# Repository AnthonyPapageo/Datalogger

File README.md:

# Datalogger
Datalogger with LCD interface

TFE Bachelier, c'était cool Thales !

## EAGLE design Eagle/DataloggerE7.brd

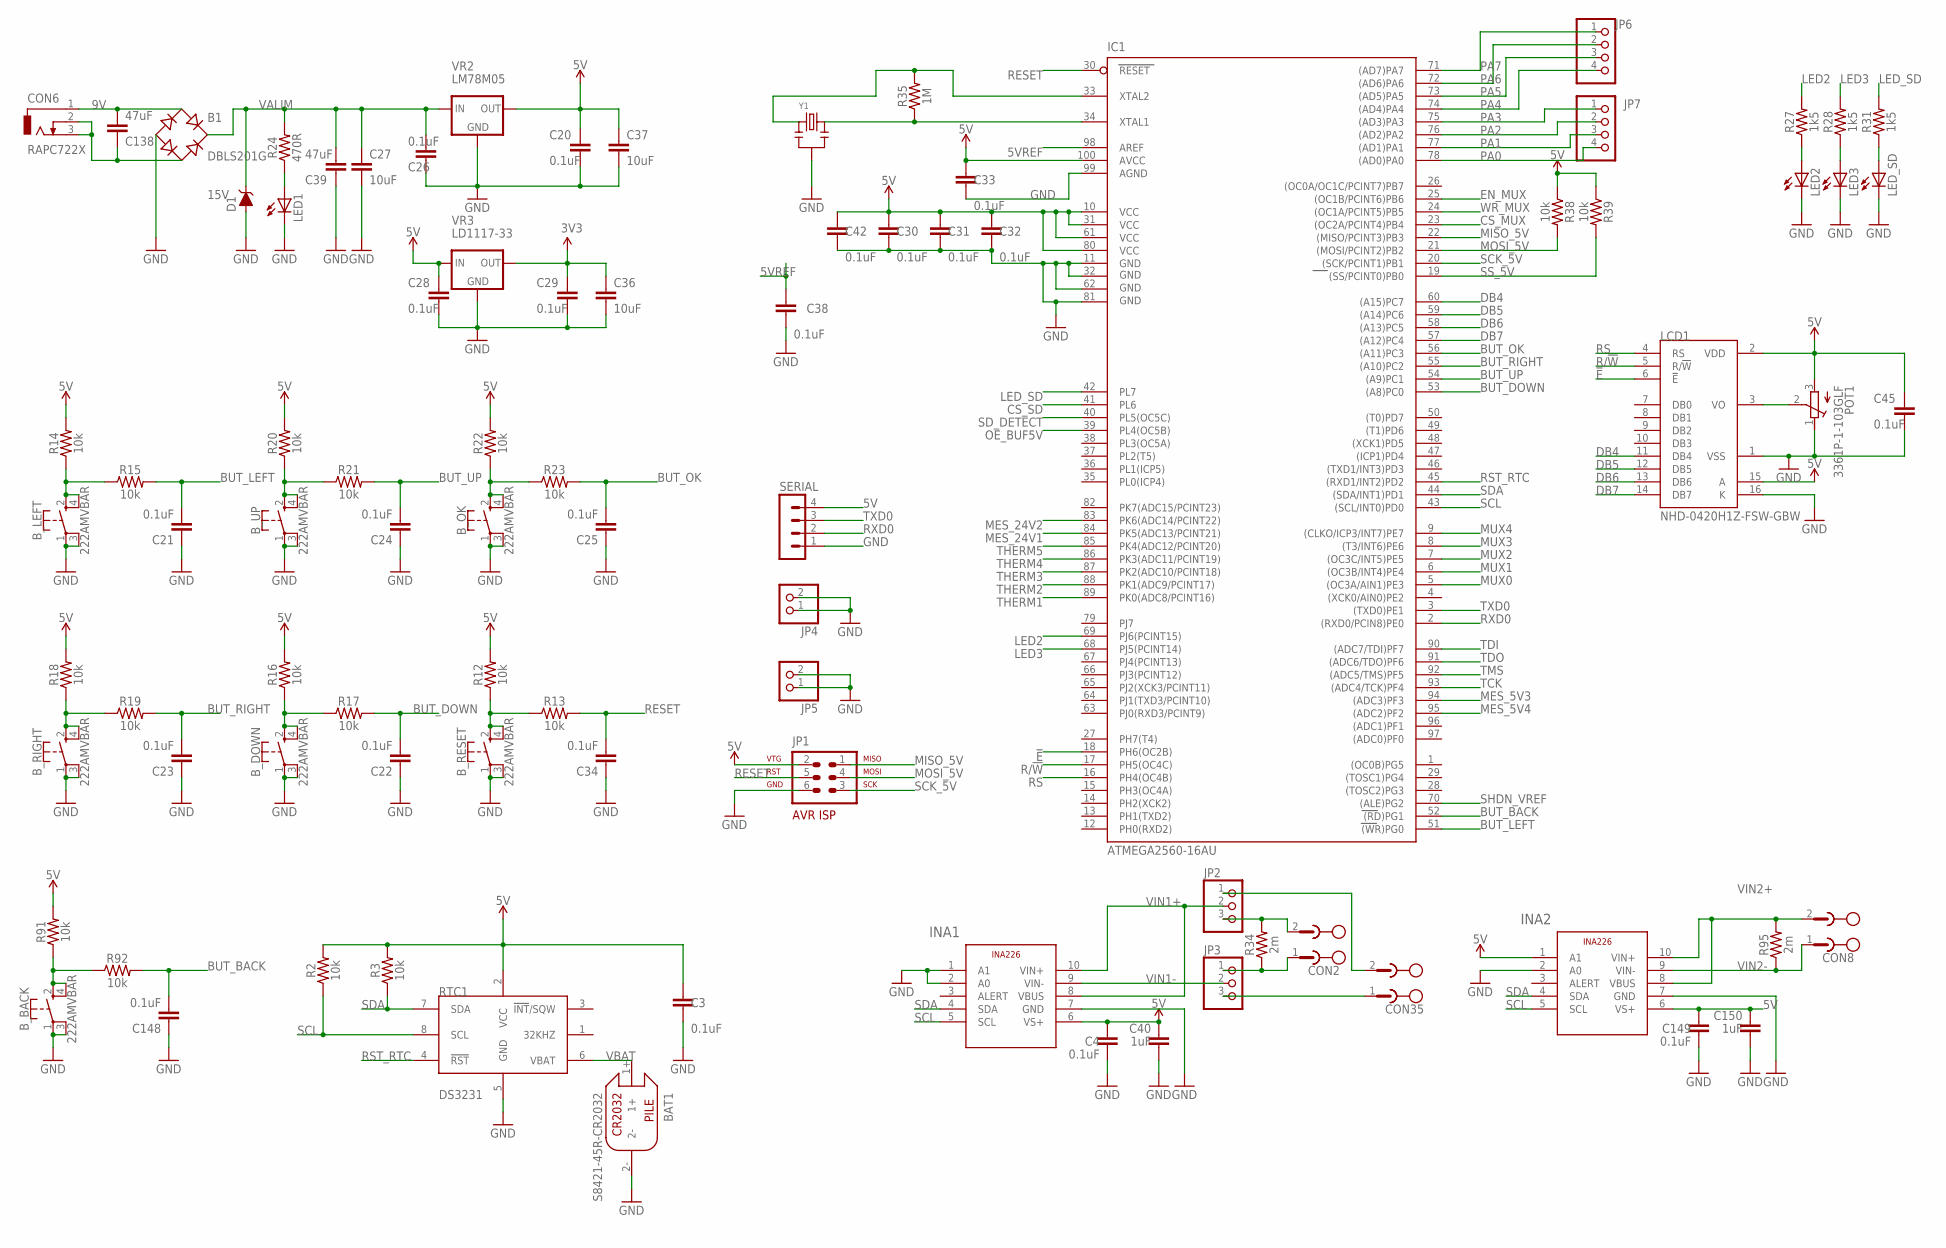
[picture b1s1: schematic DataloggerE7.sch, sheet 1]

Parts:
B1: DBLS201G; DBS
BAT1: S8421-45R-CR2032
B_BACK: 222AMVBAR; 222AMVBARSWITCH
B_DOWN: 222AMVBAR; 222AMVBARSWITCH
B_LEFT: 222AMVBAR; 222AMVBARSWITCH
B_OK: 222AMVBAR; 222AMVBARSWITCH
B_RESET: 222AMVBAR; 222AMVBARSWITCH
B_RIGHT: 222AMVBAR; 222AMVBARSWITCH
B_UP: 222AMVBAR; 222AMVBARSWITCH
C3, C4, C20, C21, C22, C23, C24, C25, C26, C28, C29, C30, C31, C32, C33, C34, C38, C42, C45, C148, C149: 0.1uF; 0603
C27, C36, C37: 10uF; 1206
C39, C138: 47uF; 1206
C40, C150: 1uF; 0603
CON2, CON8, CON35: CON_PHOENIX_508_2; MSTBV2
CON6: RAPC722X; JACK_RAPC722X
D1: DIODE-ZENER-MMSZ5232BS; SOD-323
IC1: ATMEGA2560-16AU; TQFP100
INA1, INA2: TI-INA226
JP1: AVR-ISP-6
JP2, JP3: PINHD-1X3; 1X03
JP4, JP5: PINHD-1X2; 1X02
JP6, JP7: PINHD-1X4; 1X04
LCD1: NHD-0420H1Z-FSW-GBW; LCD_2X8PINS
LED1, LED2, LED3: LEDSMT1206; 1206
LED_SD: LEDSMT1206; 1206
POT1: 3361P-1-103GLF; TRIMMER_BOURNS_SMD
R2, R3, R12, R13, R14, R15, R16, R17, R18, R19, R20, R21, R22, R23, R38, R39, R91, R92: 10k; 0603
R24: 470R; 1206
R27, R28, R31: 1k5; 0603
R34, R95: 2m; R2010
R35: 1M; 0603
RTC1: DS3231M; SOIC8
SERIAL: MA04-1
VR2: LM78M05; TO-252
VR3: LD1117-33; SOT223-THERMAL
Y1: CSTCE16M0V53-R0; CSTCE_V

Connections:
3V3: C29.1, C36.1, VR3.2 (OUT), VR3.4 (OUT); also elsewhere on the board
5V: C3.1, C4.2, C20.1, C28.1, C30.1, C31.1, C32.1, C33.1, C37.1, C40.2, C42.1, C45.1, C149.2, C150.2, IC1.10 (VCC), IC1.31 (VCC1), IC1.61 (VCC2), IC1.80 (VCC3), IC1.100 (AVCC), INA1.6 (VS+), INA2.1 (A1), INA2.6 (VS+), JP1.2, LCD1.2 (VDD), LCD1.15 (A), POT1.3 (A), R2.2, R3.2, R12.2, R14.2, R16.2, R18.2, R20.2, R22.2, R38.1, R39.1, R91.2, RTC1.2 (VCC), SERIAL.4, VR2.2 (OUT), VR3.3 (IN); also elsewhere on the board
5VREF: C38.1, IC1.98 (AREF); also elsewhere on the board
9V: B1.AC1, C138.1, CON6.1
!E!: IC1.18 (PH6(OC2B)), LCD1.6 (!E)
BUT_BACK: C148.2, IC1.52 ((RD)PG1), R92.2
BUT_DOWN: C22.2, IC1.53 ((A8)PC0), R17.2
BUT_LEFT: C21.2, IC1.51 ((WR)PG0), R15.2
BUT_OK: C25.2, IC1.56 ((A11)PC3), R23.2
BUT_RIGHT: C23.2, IC1.55 ((A10)PC2), R19.2
BUT_UP: C24.2, IC1.54 ((A9)PC1), R21.2
CS_MUX: IC1.23 ((OC2A/PCINT4)PB4); also elsewhere on the board
CS_SD: IC1.41 (PL6); also elsewhere on the board
DB4: IC1.60 ((A15)PC7), LCD1.11 (DB4)
DB5: IC1.59 ((A14)PC6), LCD1.12 (DB5)
DB6: IC1.58 ((A13)PC5), LCD1.13 (DB6)
DB7: IC1.57 ((A12)PC4), LCD1.14 (DB7)
EN_MUX: IC1.25 ((OC1B/PCINT6)PB6); also elsewhere on the board
GND: B1.-, BAT1.2-, B_BACK.1, B_BACK.3 (2), B_DOWN.1, B_DOWN.3 (2), B_LEFT.1, B_LEFT.3 (2), B_OK.1, B_OK.3 (2), B_RESET.1, B_RESET.3 (2), B_RIGHT.1, B_RIGHT.3 (2), B_UP.1, B_UP.3 (2), C3.2, C4.1, C20.2, C21.1, C22.1, C23.1, C24.1, C25.1, C26.2, C27.2, C28.2, C29.2, C30.2, C31.2, C32.2, C33.2, C34.1, C36.2, C37.2, C38.2, C39.2, C40.1, C42.2, C45.2, C148.1, C149.1, C150.1, D1.A, IC1.11 (GND), IC1.32 (GND1), IC1.62 (GND2), IC1.81 (GND3), IC1.99 (AGND), INA1.1 (A1), INA1.2 (A0), INA1.7 (GND), INA2.2 (A0), INA2.7 (GND), JP1.6, JP4.1, JP4.2, JP5.1, JP5.2, LCD1.1 (VSS), LCD1.16 (K), LED1.C, LED2.C, LED3.C, LED_SD.C, POT1.1 (E), RTC1.5 (GND), SERIAL.1, VR2.3 (GND), VR3.1 (GND), Y1.2 (GND); also elsewhere on the board
LED2: IC1.69 (PJ6(PCINT15)), R27.2
LED3: IC1.68 (PJ5(PCINT14)), R28.2
LED_SD: IC1.42 (PL7), R31.2
MES_5V3: IC1.94 ((ADC3)PF3); also elsewhere on the board
MES_5V4: IC1.95 ((ADC2)PF2); also elsewhere on the board
MES_24V1: IC1.84 (PK5(ADC13/PCINT21)); also elsewhere on the board
MES_24V2: IC1.83 (PK6(ADC14/PCINT22)); also elsewhere on the board
MISO_5V: IC1.22 ((MISO/PCINT3)PB3), JP1.1; also elsewhere on the board
MOSI_5V: IC1.21 ((MOSI/PCINT2)PB2), JP1.4, R38.2; also elsewhere on the board
MUX0: IC1.5 ((OC3A/AIN1)PE3); also elsewhere on the board
MUX1: IC1.6 ((OC3B/INT4)PE4); also elsewhere on the board
MUX2: IC1.7 ((OC3C/INT5)PE5); also elsewhere on the board
MUX3: IC1.8 ((T3/INT6)PE6); also elsewhere on the board
MUX4: IC1.9 ((CLKO/ICP3/INT7)PE7); also elsewhere on the board
unnamed: B1.AC2, C138.2, CON6.2, CON6.3
unnamed: B_LEFT.2 (3), B_LEFT.4, R14.1, R15.1
unnamed: B_DOWN.2 (3), B_DOWN.4, R16.1, R17.1
unnamed: B_RIGHT.2 (3), B_RIGHT.4, R18.1, R19.1
unnamed: B_UP.2 (3), B_UP.4, R20.1, R21.1
unnamed: B_OK.2 (3), B_OK.4, R22.1, R23.1
unnamed: B_RESET.2 (3), B_RESET.4, R12.1, R13.1
unnamed: LED1.A, R24.1
unnamed: LCD1.3 (VO), POT1.2 (S)
unnamed: LED_SD.A, R31.1
unnamed: LED2.A, R27.1
unnamed: CON2.1, JP3.1, R34.1
unnamed: CON2.2, JP2.3, R34.2
unnamed: CON35.2, JP2.1
unnamed: CON35.1, JP3.3
unnamed: LED3.A, R28.1
unnamed: B_BACK.2 (3), B_BACK.4, R91.1, R92.1
OE_BUF5V: IC1.39 (PL4(OC5B)); also elsewhere on the board
PA0: IC1.78 ((AD0)PA0), JP7.4
PA1: IC1.77 ((AD1)PA1), JP7.3
PA2: IC1.76 ((AD2)PA2), JP7.2
PA3: IC1.75 ((AD3)PA3), JP7.1
PA4: IC1.74 ((AD4)PA4), JP6.4
PA5: IC1.73 ((AD5)PA5), JP6.3
PA6: IC1.72 ((AD6)PA6), JP6.2
PA7: IC1.71 ((AD7)PA7), JP6.1
R/!W!: IC1.17 (PH5(OC4C)), LCD1.5 (R/!W)
RESET: C34.2, IC1.30 (RESET), JP1.5, R13.2; also elsewhere on the board
RS: IC1.16 (PH4(OC4B)), LCD1.4 (RS)
RST_RTC: IC1.45 ((RXD1/INT2)PD2), RTC1.4 (!RST!)
RXD0: IC1.2 ((RXD0/PCIN8)PE0), SERIAL.2
SCK_5V: IC1.20 ((SCK/PCINT1)PB1), JP1.3; also elsewhere on the board
SCL: IC1.43 ((SCL/INT0)PD0), INA1.5 (SCL), INA2.5 (SCL), R2.1, RTC1.8 (SCL)
SDA: IC1.44 ((SDA/INT1)PD1), INA1.4 (SDA), INA2.4 (SDA), R3.1, RTC1.7 (SDA)
SD_DETECT: IC1.40 (PL5(OC5C)); also elsewhere on the board
SHDN_VREF: IC1.70 ((ALE)PG2); also elsewhere on the board
SS_5V: IC1.19 ((SS/PCINT0)PB0), R39.2; also elsewhere on the board
TCK: IC1.93 ((ADC4/TCK)PF4); also elsewhere on the board
TDI: IC1.90 ((ADC7/TDI)PF7); also elsewhere on the board
TDO: IC1.91 ((ADC6/TDO)PF6); also elsewhere on the board
THERM1: IC1.89 (PK0(ADC8/PCINT16)); also elsewhere on the board
THERM2: IC1.88 (PK1(ADC9/PCINT17)); also elsewhere on the board
THERM3: IC1.87 (PK2(ADC10/PCINT18)); also elsewhere on the board
THERM4: IC1.86 (PK3(ADC11/PCINT19)); also elsewhere on the board
THERM5: IC1.85 (PK4(ADC12/PCINT20)); also elsewhere on the board
TMS: IC1.92 ((ADC5/TMS)PF5); also elsewhere on the board
TXD0: IC1.3 ((TXD0)PE1), SERIAL.3
VALIM: B1.+, C26.1, C27.1, C39.1, D1.C, R24.2, VR2.1 (IN); also elsewhere on the board
VBAT: BAT1.1+, RTC1.6 (VBAT)
VIN1+: INA1.8 (VBUS), INA1.10 (VIN+), JP2.2
VIN1-: INA1.9 (VIN-), JP3.2
VIN2+: CON8.2, INA2.8 (VBUS), INA2.10 (VIN+), R95.2
VIN2-: CON8.1, INA2.9 (VIN-), R95.1
WR_MUX: IC1.24 ((OC1A/PCINT5)PB5); also elsewhere on the board
XTAL1: IC1.34 (XTAL1), R35.1, Y1.3
XTAL2: IC1.33 (XTAL2), R35.2, Y1.1

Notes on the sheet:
15V

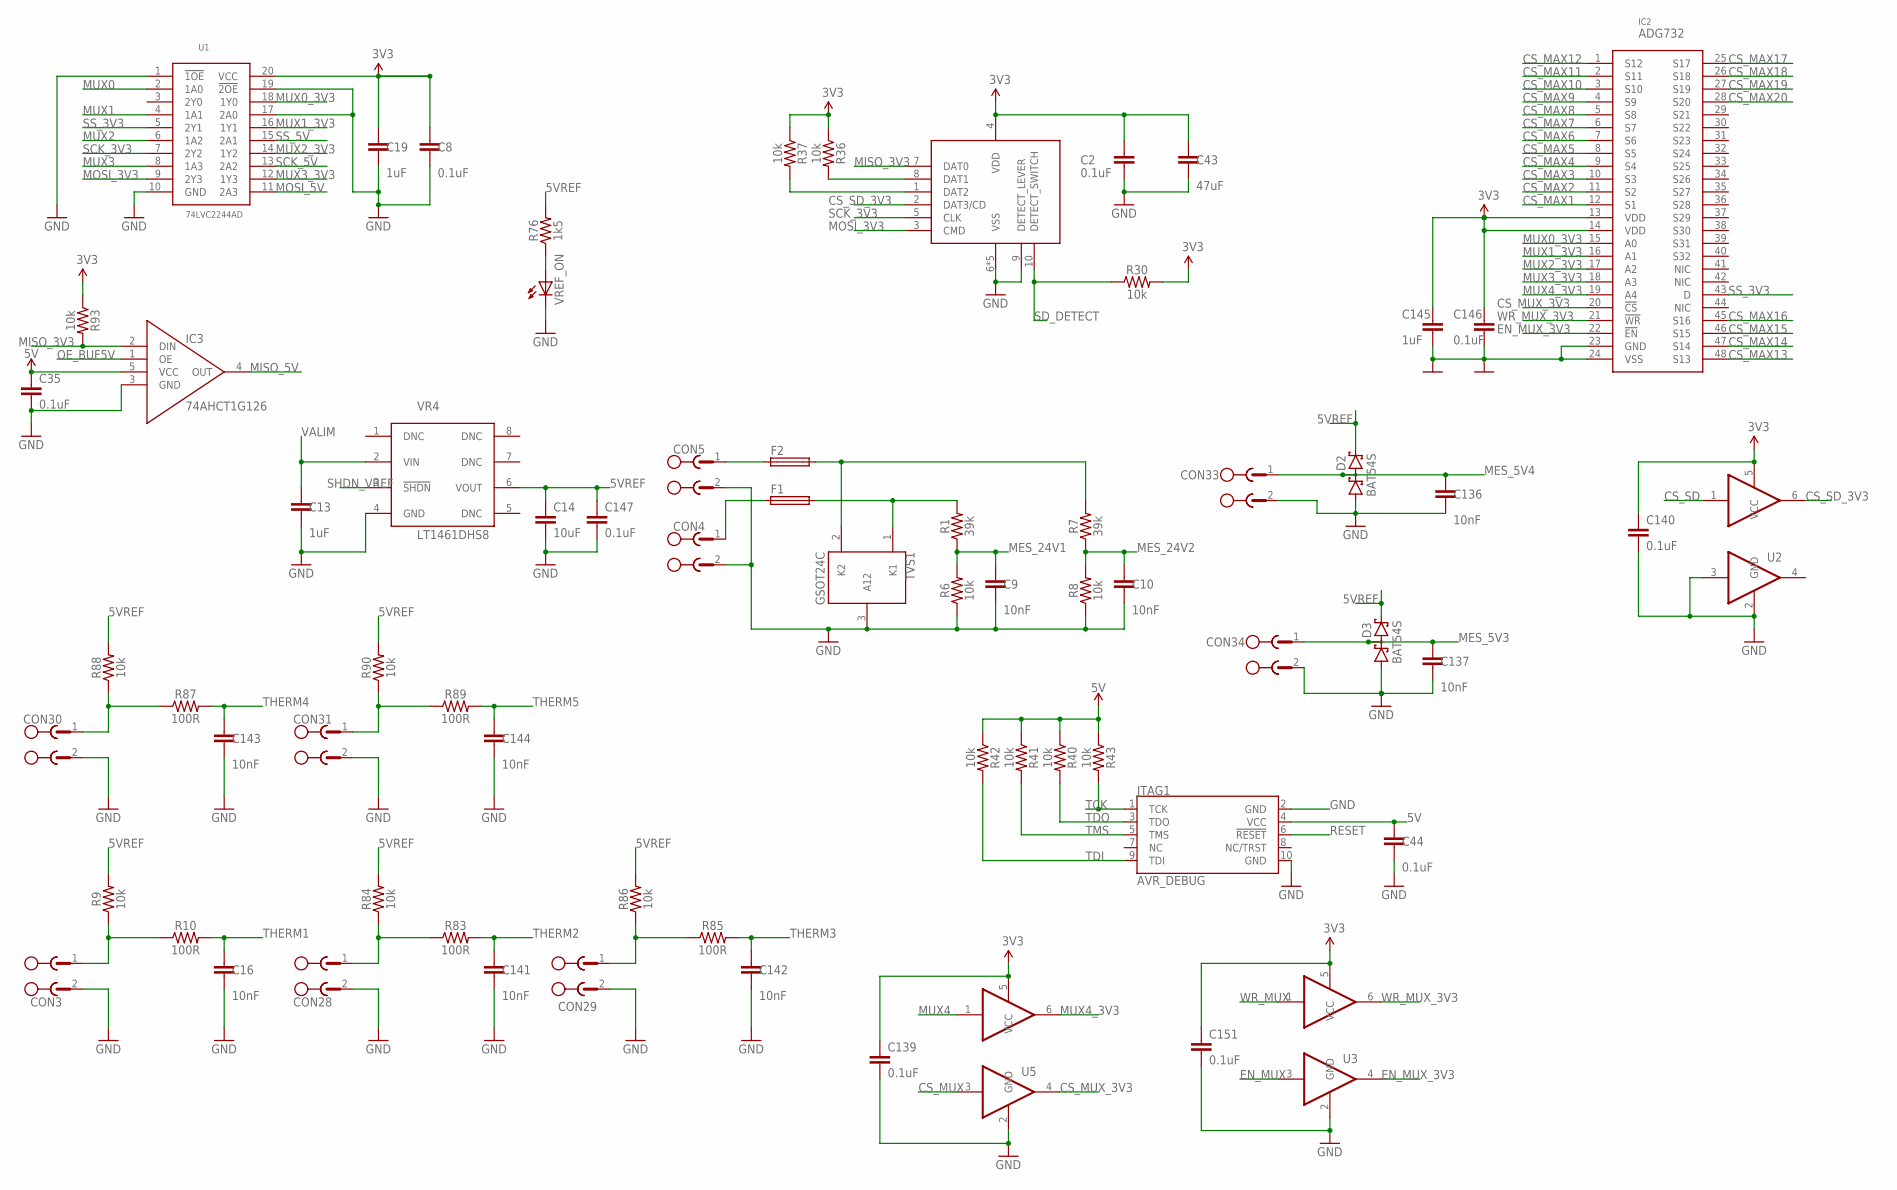
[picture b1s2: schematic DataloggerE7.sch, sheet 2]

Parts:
C2, C8, C35, C44, C139, C140, C146, C147, C151: 0.1uF; 0603
C9, C10, C16, C136, C137, C141, C142, C143, C144: 10nF; 0603
C13, C19, C145: 1uF; 0603
C14: 10uF; 1206
C43: 47uF; 1206
CON3, CON4, CON5, CON28, CON29, CON30, CON31, CON33, CON34: CON_PHOENIX_508_2; MSTBV2
CON7: MOLEX_5033981892; CONNECTOR_SDCARD_5033981892
D2, D3: BAT54S; SOT23
F1, F2: 0ZCJ0005FF2E; 0ZCJ_SERIES
IC2: ADG732; QFP50P900X900X105-48
IC3: 74AHCT1G126; SOT353
JTAG1: AVR_DEBUG; 2X5-PTH-1.27MM
R1, R7: 39k; 0603
R6, R8, R9, R30, R36, R37, R40, R41, R42, R43, R84, R86, R88, R90, R93: 10k; 0603
R10, R83, R85, R87, R89: 100R; 0603
R76: 1k5; 0603
TVS1: GSOT24C; SOT23_3PAD
U1: 74LVC2244AD; SOIC20
U2, U3, U5: 74LVC2G17SOT363; SOT363
VR4: LT1461DHS8; SOIC8-LT1461
VREF_ON: LEDSMT1206; 1206

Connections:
3V3: C2.1, C8.1, C19.1, C43.1, C139.1, C140.1, C145.1, C146.1, C151.1, CON7.4 (VDD), IC2.13 (VDD), IC2.14 (VDD), R30.2, R36.1, R37.1, R93.1, U1.20 (VCC), U2.5 (VCC), U3.5 (VCC), U5.5 (VCC); also elsewhere on the board
5V: C35.1, C44.1, IC3.5 (VCC), JTAG1.4 (VCC), R40.1, R41.1, R42.1, R43.1; also elsewhere on the board
5VREF: C14.1, C147.1, D2.2 (C2), D3.2 (C2), R9.2, R76.2, R84.2, R86.2, R88.2, R90.2, VR4.6 (VOUT); also elsewhere on the board
CS_MAX1: IC2.12 (S1); also elsewhere on the board
CS_MAX2: IC2.11 (S2); also elsewhere on the board
CS_MAX3: IC2.10 (S3); also elsewhere on the board
CS_MAX4: IC2.9 (S4); also elsewhere on the board
CS_MAX5: IC2.8 (S5); also elsewhere on the board
CS_MAX6: IC2.7 (S6); also elsewhere on the board
CS_MAX7: IC2.6 (S7); also elsewhere on the board
CS_MAX8: IC2.5 (S8); also elsewhere on the board
CS_MAX9: IC2.4 (S9); also elsewhere on the board
CS_MAX10: IC2.3 (S10); also elsewhere on the board
CS_MAX11: IC2.2 (S11); also elsewhere on the board
CS_MAX12: IC2.1 (S12); also elsewhere on the board
CS_MAX13: IC2.48 (S13); also elsewhere on the board
CS_MAX14: IC2.47 (S14); also elsewhere on the board
CS_MAX15: IC2.46 (S15); also elsewhere on the board
CS_MAX16: IC2.45 (S16); also elsewhere on the board
CS_MAX17: IC2.25 (S17); also elsewhere on the board
CS_MAX18: IC2.26 (S18); also elsewhere on the board
CS_MAX19: IC2.27 (S19); also elsewhere on the board
CS_MAX20: IC2.28 (S20); also elsewhere on the board
CS_MUX: U5.3 (I1); also elsewhere on the board
CS_MUX_3V3: IC2.20 (!CS), U5.4 (O1)
CS_SD: U2.1 (I); also elsewhere on the board
CS_SD_3V3: CON7.2 (DAT3/CD), U2.6 (O)
EN_MUX: U3.3 (I1); also elsewhere on the board
EN_MUX_3V3: IC2.22 (!EN), U3.4 (O1)
GND: C2.2, C8.2, C9.2, C10.2, C13.2, C14.2, C16.2, C19.2, C35.2, C43.2, C44.2, C136.2, C137.2, C139.2, C140.2, C141.2, C142.2, C143.2, C144.2, C145.2, C146.2, C147.2, C151.2, CON3.2, CON4.2, CON5.2, CON7.6 (VSS), CON7.9 (DETECT_LEVER), CON7.11 (VSS), CON7.12 (VSS), CON7.13 (VSS), CON7.14 (VSS), CON28.2, CON29.2, CON30.2, CON31.2, CON33.2, CON34.2, D2.1 (A1), D3.1 (A1), IC2.23 (GND), IC2.24 (VSS), IC3.3 (GND), JTAG1.2 (GND), JTAG1.10 (GND), R6.1, R8.1, TVS1.3 (A12), U1.1 (!1OE!), U1.10 (GND), U1.17 (2A0), U1.19 (!2OE!), U2.2 (GND), U2.3 (I1), U3.2 (GND), U5.2 (GND), VR4.4 (GND), VREF_ON.C; also elsewhere on the board
MES_5V3: C137.1, CON34.1, D3.3 (C1A2); also elsewhere on the board
MES_5V4: C136.1, CON33.1, D2.3 (C1A2); also elsewhere on the board
MES_24V1: C9.1, R1.1, R6.2; also elsewhere on the board
MES_24V2: C10.1, R7.1, R8.2; also elsewhere on the board
MISO_3V3: CON7.7 (DAT0), IC3.2 (DIN), R93.2; also elsewhere on the board
MISO_5V: IC3.4 (OUT); also elsewhere on the board
MOSI_3V3: CON7.3 (CMD), U1.9 (2Y3); also elsewhere on the board
MOSI_5V: U1.11 (2A3); also elsewhere on the board
MUX0: U1.2 (1A0); also elsewhere on the board
MUX0_3V3: IC2.15 (A0), U1.18 (1Y0)
MUX1: U1.4 (1A1); also elsewhere on the board
MUX1_3V3: IC2.16 (A1), U1.16 (1Y1)
MUX2: U1.6 (1A2); also elsewhere on the board
MUX2_3V3: IC2.17 (A2), U1.14 (1Y2)
MUX3: U1.8 (1A3); also elsewhere on the board
MUX3_3V3: IC2.18 (A3), U1.12 (1Y3)
MUX4: U5.1 (I); also elsewhere on the board
MUX4_3V3: IC2.19 (A4), U5.6 (O)
unnamed: F2.2, R7.2, TVS1.2 (K2)
unnamed: CON7.8 (DAT1), R36.2
unnamed: CON7.1 (DAT2), R37.2
unnamed: CON3.1, R9.1, R10.1
unnamed: F1.2, R1.2, TVS1.1 (K1)
unnamed: CON5.1, F2.1
unnamed: CON30.1, R87.1, R88.1
unnamed: CON29.1, R85.1, R86.1
unnamed: CON4.1, F1.1
unnamed: CON28.1, R83.1, R84.1
unnamed: R76.1, VREF_ON.A
unnamed: CON31.1, R89.1, R90.1
OE_BUF5V: IC3.1 (OE); also elsewhere on the board
RESET: JTAG1.6 (!RESET!); also elsewhere on the board
SCK_3V3: CON7.5 (CLK), U1.7 (2Y2); also elsewhere on the board
SCK_5V: U1.13 (2A2); also elsewhere on the board
SD_DETECT: CON7.10 (DETECT_SWITCH), R30.1; also elsewhere on the board
SHDN_VREF: VR4.3 (!SHDN!); also elsewhere on the board
SS_3V3: IC2.43 (D), U1.5 (2Y1)
SS_5V: U1.15 (2A1); also elsewhere on the board
TCK: JTAG1.1 (TCK), R43.2; also elsewhere on the board
TDI: JTAG1.9 (TDI), R42.2; also elsewhere on the board
TDO: JTAG1.3 (TDO), R40.2; also elsewhere on the board
THERM1: C16.1, R10.2; also elsewhere on the board
THERM2: C141.1, R83.2; also elsewhere on the board
THERM3: C142.1, R85.2; also elsewhere on the board
THERM4: C143.1, R87.2; also elsewhere on the board
THERM5: C144.1, R89.2; also elsewhere on the board
TMS: JTAG1.5 (TMS), R41.2; also elsewhere on the board
VALIM: C13.1, VR4.2 (VIN); also elsewhere on the board
WR_MUX: U3.1 (I); also elsewhere on the board
WR_MUX_3V3: IC2.21 (!WR), U3.6 (O)

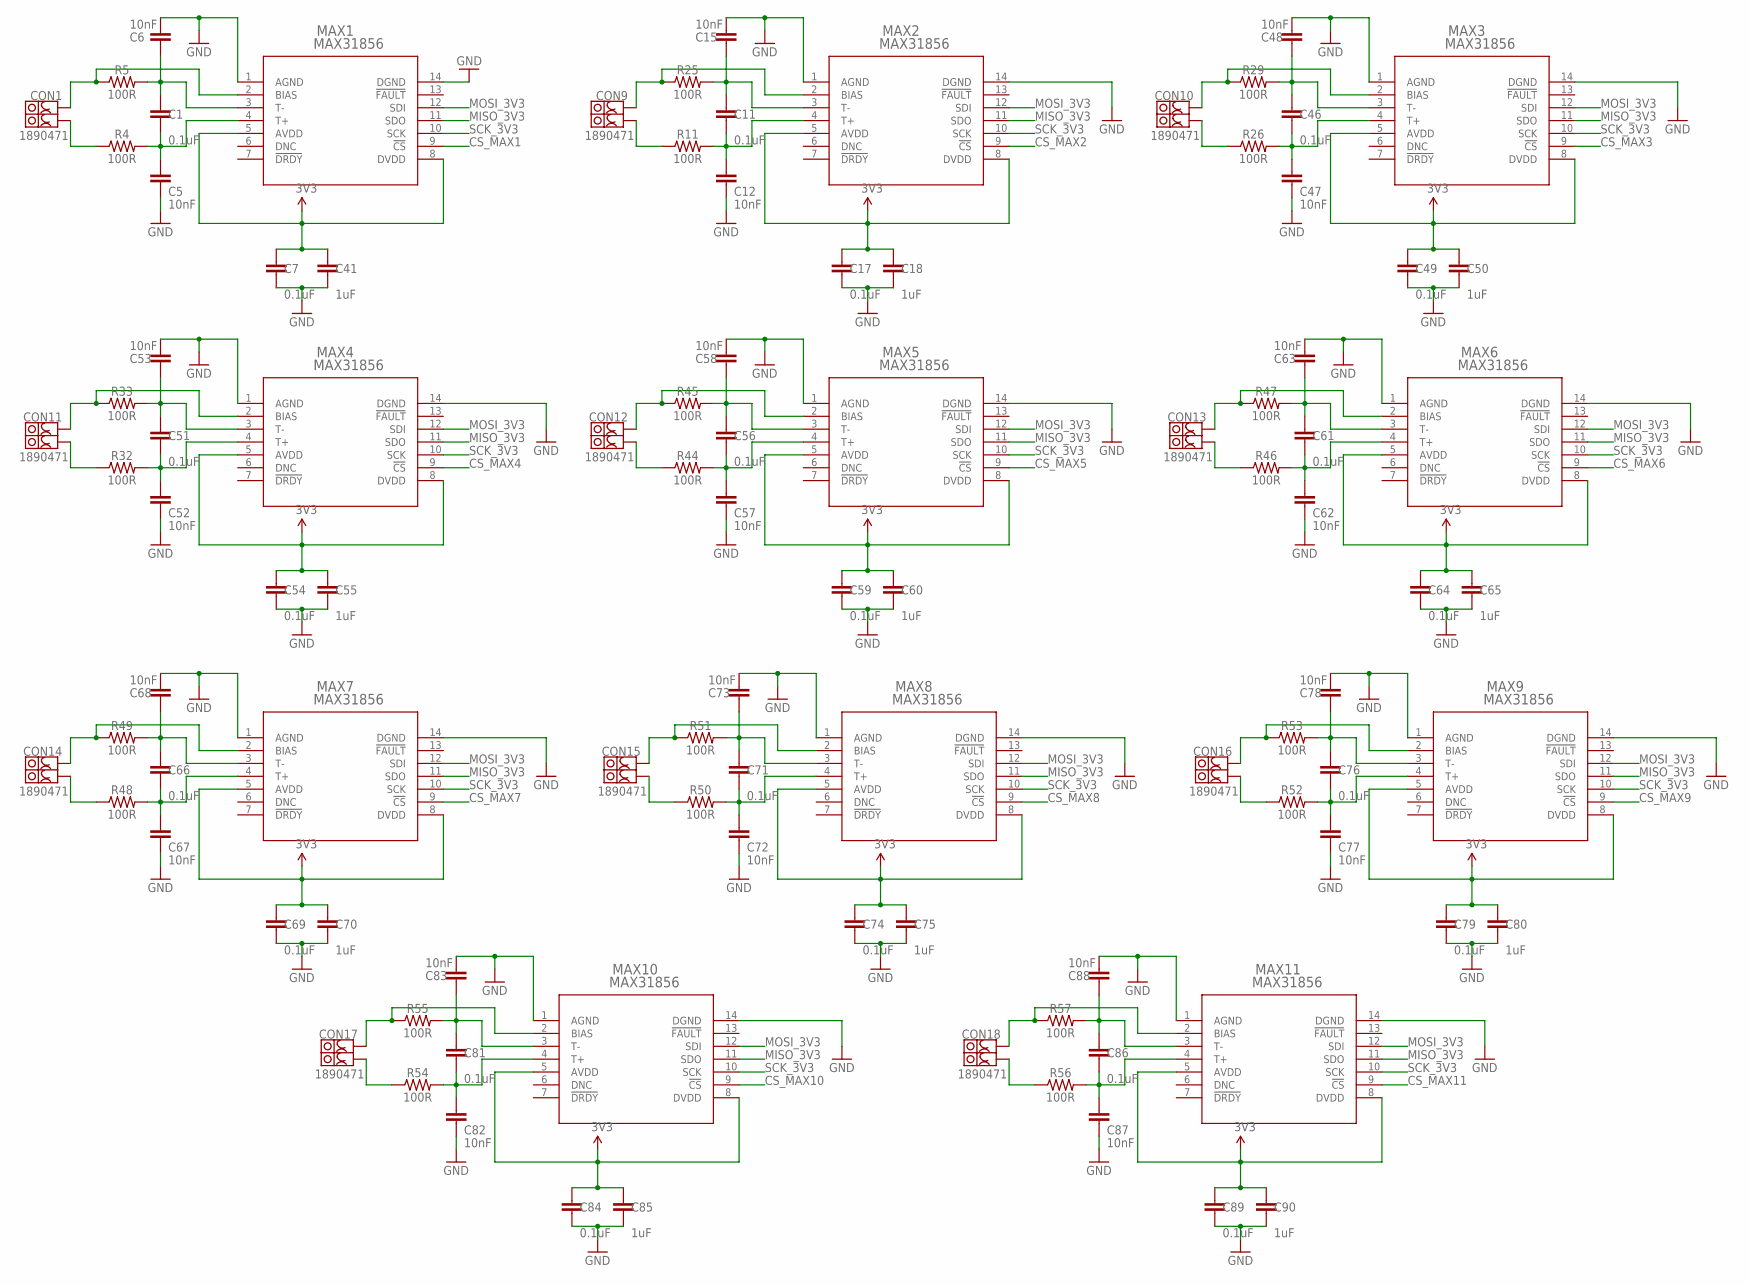
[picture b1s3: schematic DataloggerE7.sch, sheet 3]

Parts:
C1, C7, C11, C17, C46, C49, C51, C54, C56, C59, C61, C64, C66, C69, C71, C74, C76, C79, C81, C84, C86, C89: 0.1uF; 0603
C5, C6, C12, C15, C47, C48, C52, C53, C57, C58, C62, C63, C67, C68, C72, C73, C77, C78, C82, C83, C87, C88: 10nF; 0603
C18, C41, C50, C55, C60, C65, C70, C75, C80, C85, C90: 1uF; 0603
CON1, CON9, CON10, CON11, CON12, CON13, CON14, CON15, CON16, CON17, CON18: 1890471
MAX1, MAX2, MAX3, MAX4, MAX5, MAX6, MAX7, MAX8, MAX9, MAX10, MAX11: MAX31856; 21-066J-14-M
R4, R5, R11, R25, R26, R29, R32, R33, R44, R45, R46, R47, R48, R49, R50, R51, R52, R53, R54, R55, R56, R57: 100R; 0603

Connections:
3V3: C7.1, C17.1, C18.1, C41.1, C49.1, C50.1, C54.1, C55.1, C59.1, C60.1, C64.1, C65.1, C69.1, C70.1, C74.1, C75.1, C79.1, C80.1, C84.1, C85.1, C89.1, C90.1, MAX1.5 (AVDD), MAX1.8 (DVDD), MAX2.5 (AVDD), MAX2.8 (DVDD), MAX3.5 (AVDD), MAX3.8 (DVDD), MAX4.5 (AVDD), MAX4.8 (DVDD), MAX5.5 (AVDD), MAX5.8 (DVDD), MAX6.5 (AVDD), MAX6.8 (DVDD), MAX7.5 (AVDD), MAX7.8 (DVDD), MAX8.5 (AVDD), MAX8.8 (DVDD), MAX9.5 (AVDD), MAX9.8 (DVDD), MAX10.5 (AVDD), MAX10.8 (DVDD), MAX11.5 (AVDD), MAX11.8 (DVDD); also elsewhere on the board
BIAS: CON1.A (1A), CON1.B (1A), MAX1.2 (BIAS), R5.1
BIAS1: CON9.A (1A), CON9.B (1A), MAX2.2 (BIAS), R25.1
BIAS2: CON10.A (1A), CON10.B (1A), MAX3.2 (BIAS), R29.1
BIAS3: CON11.A (1A), CON11.B (1A), MAX4.2 (BIAS), R33.1
BIAS5: CON12.A (1A), CON12.B (1A), MAX5.2 (BIAS), R45.1
BIAS6: CON13.A (1A), CON13.B (1A), MAX6.2 (BIAS), R47.1
BIAS7: CON14.A (1A), CON14.B (1A), MAX7.2 (BIAS), R49.1
BIAS8: CON15.A (1A), CON15.B (1A), MAX8.2 (BIAS), R51.1
BIAS9: CON16.A (1A), CON16.B (1A), MAX9.2 (BIAS), R53.1
BIAS10: CON17.A (1A), CON17.B (1A), MAX10.2 (BIAS), R55.1
BIAS11: CON18.A (1A), CON18.B (1A), MAX11.2 (BIAS), R57.1
CS_MAX1: MAX1.9 (!CS); also elsewhere on the board
CS_MAX2: MAX2.9 (!CS); also elsewhere on the board
CS_MAX3: MAX3.9 (!CS); also elsewhere on the board
CS_MAX4: MAX4.9 (!CS); also elsewhere on the board
CS_MAX5: MAX5.9 (!CS); also elsewhere on the board
CS_MAX6: MAX6.9 (!CS); also elsewhere on the board
CS_MAX7: MAX7.9 (!CS); also elsewhere on the board
CS_MAX8: MAX8.9 (!CS); also elsewhere on the board
CS_MAX9: MAX9.9 (!CS); also elsewhere on the board
CS_MAX10: MAX10.9 (!CS); also elsewhere on the board
CS_MAX11: MAX11.9 (!CS); also elsewhere on the board
GND: C5.2, C6.1, C7.2, C12.2, C15.1, C17.2, C18.2, C41.2, C47.2, C48.1, C49.2, C50.2, C52.2, C53.1, C54.2, C55.2, C57.2, C58.1, C59.2, C60.2, C62.2, C63.1, C64.2, C65.2, C67.2, C68.1, C69.2, C70.2, C72.2, C73.1, C74.2, C75.2, C77.2, C78.1, C79.2, C80.2, C82.2, C83.1, C84.2, C85.2, C87.2, C88.1, C89.2, C90.2, MAX1.1 (AGND), MAX1.14 (DGND), MAX2.1 (AGND), MAX2.14 (DGND), MAX3.1 (AGND), MAX3.14 (DGND), MAX4.1 (AGND), MAX4.14 (DGND), MAX5.1 (AGND), MAX5.14 (DGND), MAX6.1 (AGND), MAX6.14 (DGND), MAX7.1 (AGND), MAX7.14 (DGND), MAX8.1 (AGND), MAX8.14 (DGND), MAX9.1 (AGND), MAX9.14 (DGND), MAX10.1 (AGND), MAX10.14 (DGND), MAX11.1 (AGND), MAX11.14 (DGND); also elsewhere on the board
MISO_3V3: MAX1.11 (SDO), MAX2.11 (SDO), MAX3.11 (SDO), MAX4.11 (SDO), MAX5.11 (SDO), MAX6.11 (SDO), MAX7.11 (SDO), MAX8.11 (SDO), MAX9.11 (SDO), MAX10.11 (SDO), MAX11.11 (SDO); also elsewhere on the board
MOSI_3V3: MAX1.12 (SDI), MAX2.12 (SDI), MAX3.12 (SDI), MAX4.12 (SDI), MAX5.12 (SDI), MAX6.12 (SDI), MAX7.12 (SDI), MAX8.12 (SDI), MAX9.12 (SDI), MAX10.12 (SDI), MAX11.12 (SDI); also elsewhere on the board
unnamed: CON1.A1 (1A1), CON1.B1 (1A1), R4.1
unnamed: CON9.A1 (1A1), CON9.B1 (1A1), R11.1
unnamed: CON10.A1 (1A1), CON10.B1 (1A1), R26.1
unnamed: CON11.A1 (1A1), CON11.B1 (1A1), R32.1
unnamed: CON12.A1 (1A1), CON12.B1 (1A1), R44.1
unnamed: CON13.A1 (1A1), CON13.B1 (1A1), R46.1
unnamed: CON14.A1 (1A1), CON14.B1 (1A1), R48.1
unnamed: CON15.A1 (1A1), CON15.B1 (1A1), R50.1
unnamed: CON16.A1 (1A1), CON16.B1 (1A1), R52.1
unnamed: CON17.A1 (1A1), CON17.B1 (1A1), R54.1
unnamed: CON18.A1 (1A1), CON18.B1 (1A1), R56.1
SCK_3V3: MAX1.10 (SCK), MAX2.10 (SCK), MAX3.10 (SCK), MAX4.10 (SCK), MAX5.10 (SCK), MAX6.10 (SCK), MAX7.10 (SCK), MAX8.10 (SCK), MAX9.10 (SCK), MAX10.10 (SCK), MAX11.10 (SCK); also elsewhere on the board
T+: C1.2, C5.1, MAX1.4 (T+), R4.2
T+1: C11.2, C12.1, MAX2.4 (T+), R11.2
T+2: C46.2, C47.1, MAX3.4 (T+), R26.2
T+3: C51.2, C52.1, MAX4.4 (T+), R32.2
T+5: C56.2, C57.1, MAX5.4 (T+), R44.2
T+6: C61.2, C62.1, MAX6.4 (T+), R46.2
T+7: C66.2, C67.1, MAX7.4 (T+), R48.2
T+8: C71.2, C72.1, MAX8.4 (T+), R50.2
T+9: C76.2, C77.1, MAX9.4 (T+), R52.2
T+10: C81.2, C82.1, MAX10.4 (T+), R54.2
T+11: C86.2, C87.1, MAX11.4 (T+), R56.2
T-: C1.1, C6.2, MAX1.3 (T-), R5.2
T-1: C11.1, C15.2, MAX2.3 (T-), R25.2
T-2: C46.1, C48.2, MAX3.3 (T-), R29.2
T-3: C51.1, C53.2, MAX4.3 (T-), R33.2
T-5: C56.1, C58.2, MAX5.3 (T-), R45.2
T-6: C61.1, C63.2, MAX6.3 (T-), R47.2
T-7: C66.1, C68.2, MAX7.3 (T-), R49.2
T-8: C71.1, C73.2, MAX8.3 (T-), R51.2
T-9: C76.1, C78.2, MAX9.3 (T-), R53.2
T-10: C81.1, C83.2, MAX10.3 (T-), R55.2
T-11: C86.1, C88.2, MAX11.3 (T-), R57.2

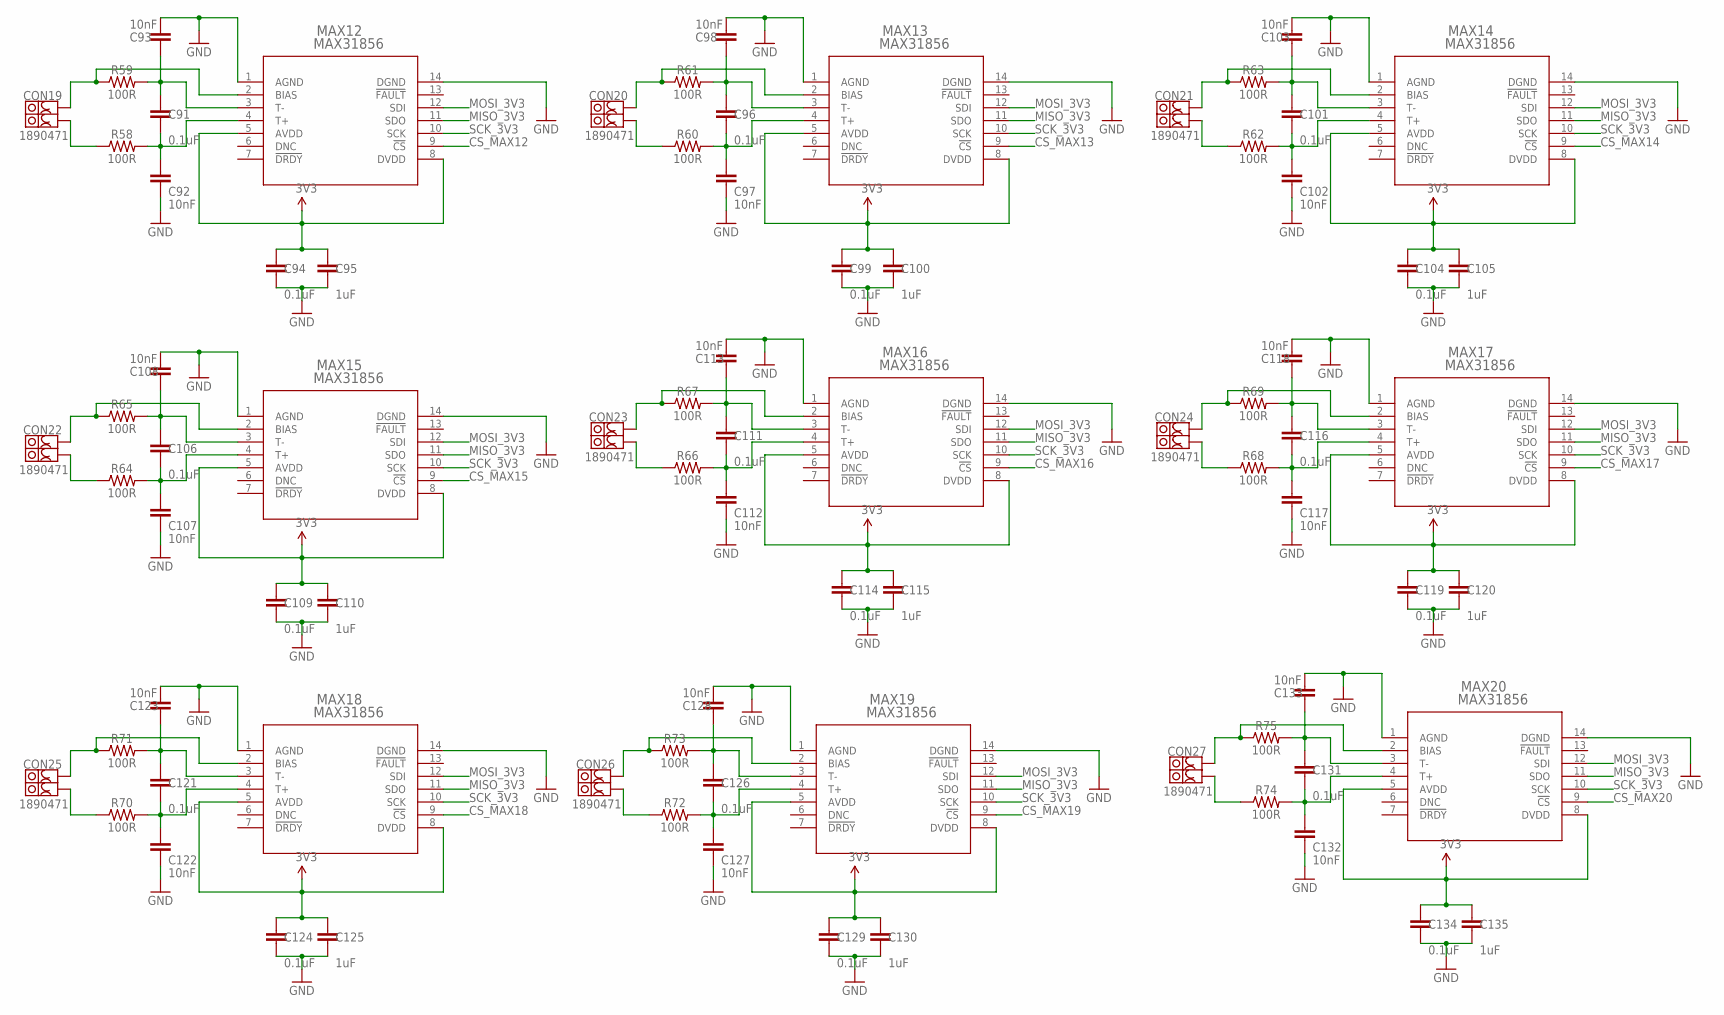
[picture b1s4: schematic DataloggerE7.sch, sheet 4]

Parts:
C91, C94, C96, C99, C101, C104, C106, C109, C111, C114, C116, C119, C121, C124, C126, C129, C131, C134: 0.1uF; 0603
C92, C93, C97, C98, C102, C103, C107, C108, C112, C113, C117, C118, C122, C123, C127, C128, C132, C133: 10nF; 0603
C95, C100, C105, C110, C115, C120, C125, C130, C135: 1uF; 0603
CON19, CON20, CON21, CON22, CON23, CON24, CON25, CON26, CON27: 1890471
MAX12, MAX13, MAX14, MAX15, MAX16, MAX17, MAX18, MAX19, MAX20: MAX31856; 21-066J-14-M
R58, R59, R60, R61, R62, R63, R64, R65, R66, R67, R68, R69, R70, R71, R72, R73, R74, R75: 100R; 0603

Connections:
3V3: C94.1, C95.1, C99.1, C100.1, C104.1, C105.1, C109.1, C110.1, C114.1, C115.1, C119.1, C120.1, C124.1, C125.1, C129.1, C130.1, C134.1, C135.1, MAX12.5 (AVDD), MAX12.8 (DVDD), MAX13.5 (AVDD), MAX13.8 (DVDD), MAX14.5 (AVDD), MAX14.8 (DVDD), MAX15.5 (AVDD), MAX15.8 (DVDD), MAX16.5 (AVDD), MAX16.8 (DVDD), MAX17.5 (AVDD), MAX17.8 (DVDD), MAX18.5 (AVDD), MAX18.8 (DVDD), MAX19.5 (AVDD), MAX19.8 (DVDD), MAX20.5 (AVDD), MAX20.8 (DVDD); also elsewhere on the board
BIAS4: CON19.A (1A), CON19.B (1A), MAX12.2 (BIAS), R59.1
BIAS12: CON20.A (1A), CON20.B (1A), MAX13.2 (BIAS), R61.1
BIAS13: CON21.A (1A), CON21.B (1A), MAX14.2 (BIAS), R63.1
BIAS14: CON22.A (1A), CON22.B (1A), MAX15.2 (BIAS), R65.1
BIAS15: CON23.A (1A), CON23.B (1A), MAX16.2 (BIAS), R67.1
BIAS16: CON24.A (1A), CON24.B (1A), MAX17.2 (BIAS), R69.1
BIAS17: CON25.A (1A), CON25.B (1A), MAX18.2 (BIAS), R71.1
BIAS18: CON26.A (1A), CON26.B (1A), MAX19.2 (BIAS), R73.1
BIAS19: CON27.A (1A), CON27.B (1A), MAX20.2 (BIAS), R75.1
CS_MAX12: MAX12.9 (!CS); also elsewhere on the board
CS_MAX13: MAX13.9 (!CS); also elsewhere on the board
CS_MAX14: MAX14.9 (!CS); also elsewhere on the board
CS_MAX15: MAX15.9 (!CS); also elsewhere on the board
CS_MAX16: MAX16.9 (!CS); also elsewhere on the board
CS_MAX17: MAX17.9 (!CS); also elsewhere on the board
CS_MAX18: MAX18.9 (!CS); also elsewhere on the board
CS_MAX19: MAX19.9 (!CS); also elsewhere on the board
CS_MAX20: MAX20.9 (!CS); also elsewhere on the board
GND: C92.2, C93.1, C94.2, C95.2, C97.2, C98.1, C99.2, C100.2, C102.2, C103.1, C104.2, C105.2, C107.2, C108.1, C109.2, C110.2, C112.2, C113.1, C114.2, C115.2, C117.2, C118.1, C119.2, C120.2, C122.2, C123.1, C124.2, C125.2, C127.2, C128.1, C129.2, C130.2, C132.2, C133.1, C134.2, C135.2, MAX12.1 (AGND), MAX12.14 (DGND), MAX13.1 (AGND), MAX13.14 (DGND), MAX14.1 (AGND), MAX14.14 (DGND), MAX15.1 (AGND), MAX15.14 (DGND), MAX16.1 (AGND), MAX16.14 (DGND), MAX17.1 (AGND), MAX17.14 (DGND), MAX18.1 (AGND), MAX18.14 (DGND), MAX19.1 (AGND), MAX19.14 (DGND), MAX20.1 (AGND), MAX20.14 (DGND); also elsewhere on the board
MISO_3V3: MAX12.11 (SDO), MAX13.11 (SDO), MAX14.11 (SDO), MAX15.11 (SDO), MAX16.11 (SDO), MAX17.11 (SDO), MAX18.11 (SDO), MAX19.11 (SDO), MAX20.11 (SDO); also elsewhere on the board
MOSI_3V3: MAX12.12 (SDI), MAX13.12 (SDI), MAX14.12 (SDI), MAX15.12 (SDI), MAX16.12 (SDI), MAX17.12 (SDI), MAX18.12 (SDI), MAX19.12 (SDI), MAX20.12 (SDI); also elsewhere on the board
unnamed: CON20.A1 (1A1), CON20.B1 (1A1), R60.1
unnamed: CON21.A1 (1A1), CON21.B1 (1A1), R62.1
unnamed: CON19.A1 (1A1), CON19.B1 (1A1), R58.1
unnamed: CON22.A1 (1A1), CON22.B1 (1A1), R64.1
unnamed: CON23.A1 (1A1), CON23.B1 (1A1), R66.1
unnamed: CON24.A1 (1A1), CON24.B1 (1A1), R68.1
unnamed: CON25.A1 (1A1), CON25.B1 (1A1), R70.1
unnamed: CON26.A1 (1A1), CON26.B1 (1A1), R72.1
unnamed: CON27.A1 (1A1), CON27.B1 (1A1), R74.1
SCK_3V3: MAX12.10 (SCK), MAX13.10 (SCK), MAX14.10 (SCK), MAX15.10 (SCK), MAX16.10 (SCK), MAX17.10 (SCK), MAX18.10 (SCK), MAX19.10 (SCK), MAX20.10 (SCK); also elsewhere on the board
T+4: C91.2, C92.1, MAX12.4 (T+), R58.2
T+12: C96.2, C97.1, MAX13.4 (T+), R60.2
T+13: C101.2, C102.1, MAX14.4 (T+), R62.2
T+14: C106.2, C107.1, MAX15.4 (T+), R64.2
T+15: C111.2, C112.1, MAX16.4 (T+), R66.2
T+16: C116.2, C117.1, MAX17.4 (T+), R68.2
T+17: C121.2, C122.1, MAX18.4 (T+), R70.2
T+18: C126.2, C127.1, MAX19.4 (T+), R72.2
T+19: C131.2, C132.1, MAX20.4 (T+), R74.2
T-4: C91.1, C93.2, MAX12.3 (T-), R59.2
T-12: C96.1, C98.2, MAX13.3 (T-), R61.2
T-13: C101.1, C103.2, MAX14.3 (T-), R63.2
T-14: C106.1, C108.2, MAX15.3 (T-), R65.2
T-15: C111.1, C113.2, MAX16.3 (T-), R67.2
T-16: C116.1, C118.2, MAX17.3 (T-), R69.2
T-17: C121.1, C123.2, MAX18.3 (T-), R71.2
T-18: C126.1, C128.2, MAX19.3 (T-), R73.2
T-19: C131.1, C133.2, MAX20.3 (T-), R75.2

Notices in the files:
parts and their libraries:
FaBo-Mems: Released under the Creative Commons Attribution-ShareAlike 4.0 License
https://creativecommons.org/licenses/by-sa/4.0
SparkFun-PowerSymbols: Licensing: Creative Commons ShareAlike 4.0 International - https://creativecommons.org/licenses/by-sa/4.0
